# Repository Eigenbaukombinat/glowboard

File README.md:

# Glowboard Plotter

The Glowboard Plotter plots images using 64 UV LEDs attached in a line moved over a 120cmx60cm glow-in-the-dark sheet by a stepper.

More Details see here: https://hackaday.io/project/11868-glowboard-plotter

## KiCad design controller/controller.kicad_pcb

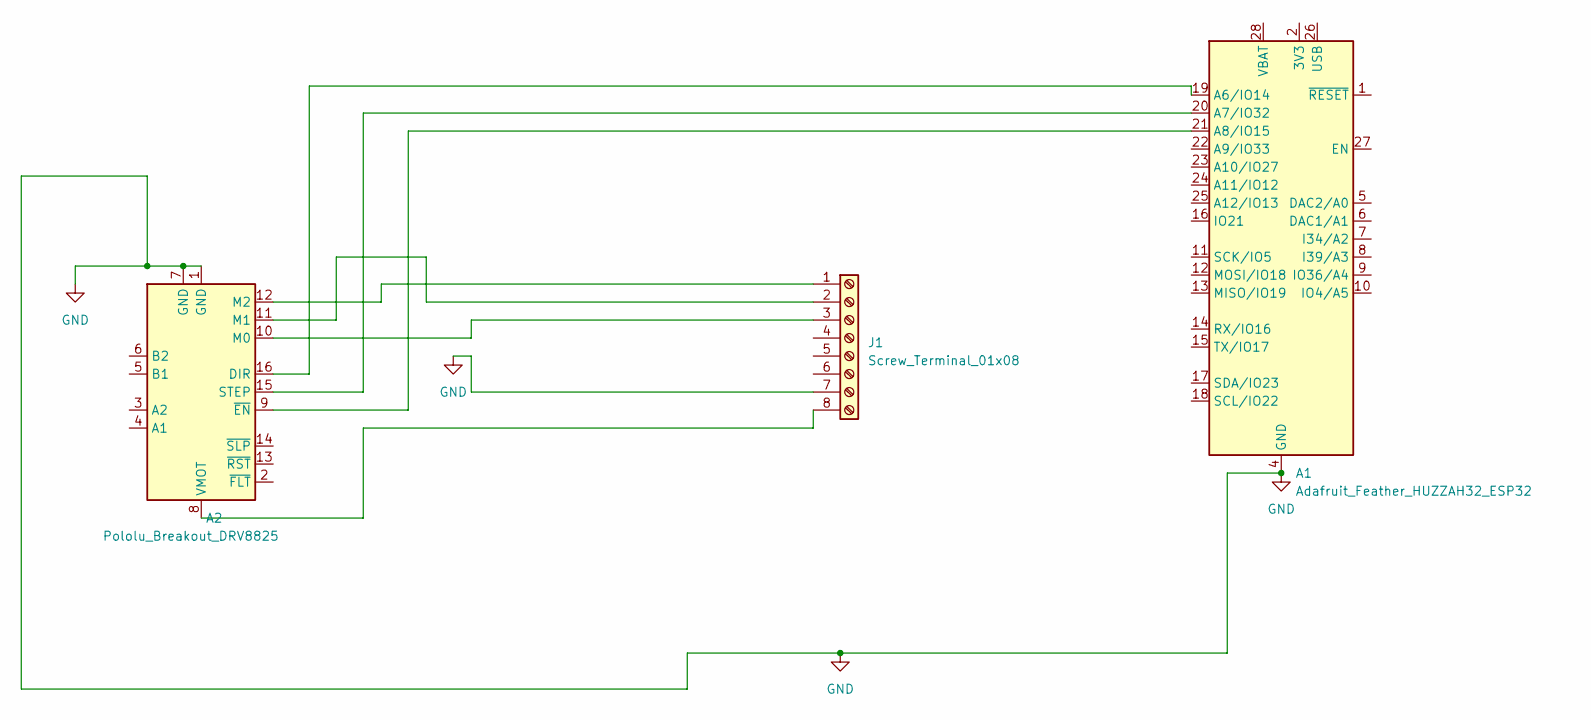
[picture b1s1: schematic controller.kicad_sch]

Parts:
A1: Adafruit_Feather_HUZZAH32_ESP32; Adafruit_Feather
A2: Pololu_Breakout_DRV8825; Pololu_Breakout-16_15.2x20.3mm
J1: Screw_Terminal_01x08; TerminalBlock_4Ucon_1x08_P3.50mm_Horizontal

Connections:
GND: A1.4 (GND), A2.1 (GND), A2.7 (GND), J1.7
unnamed: A1.19 (A6/IO14), A2.16 (DIR)
unnamed: A1.20 (A7/IO32), A2.15 (STEP)
unnamed: A1.21 (A8/IO15), A2.9 (~EN)
unnamed: A2.10 (M0), J1.3
unnamed: A2.11 (M1), J1.2
unnamed: A2.12 (M2), J1.1
unnamed: A2.8 (VMOT), J1.8

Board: 2 copper layers, 3 parts (0 on the bottom side), 8 nets, no tracks yet.

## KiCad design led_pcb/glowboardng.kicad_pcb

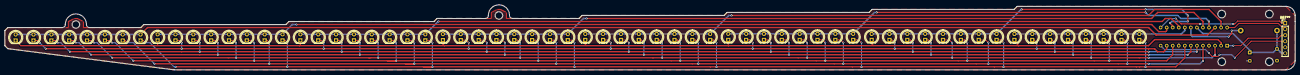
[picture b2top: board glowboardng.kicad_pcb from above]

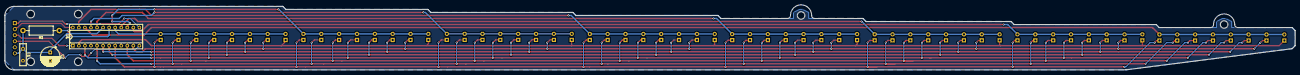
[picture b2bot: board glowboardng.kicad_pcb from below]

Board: 2 copper layers, 542.3 x 27.3 mm, 68 parts (4 on the bottom side), 19 nets.

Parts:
C1: C; C_Disc_D9.0mm_W2.5mm_P5.00mm
C2: C_Polarized; CP_Radial_D8.0mm_P3.50mm
D1, D2, D3, D4, D5, D6, D7, D8, D9, D10, D11, D12, D13, D14, D15, D16, D17, D18, D19, D20, D21, D22, D23, D24, D25, D26, D27, D28, D29, D30, D31, D32, D33, D34, D35, D36, D37, D38, D39, D40, D41, D42, D43, D44, D45, D46, D47, D48, D49, D50, D51, D52, D53, D54, D55, D56, D57, D58, D59, D60, D61, D62, D63, D64: CQY99; LED_D5.0mm_IRGrey
R1: R; R_Axial_DIN0411_L9.9mm_D3.6mm_P15.24mm_Horizontal
U1: MAX7219; DIP-24_W7.62mm_Socket

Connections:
+5V: C1.1, C2.1, R1.2, U1.19 (V+)
GND: C1.2, C2.2, U1.4 (GND), U1.9 (GND)
unnamed: D1.2 (A), D2.2 (A), D3.2 (A), D4.2 (A), D5.2 (A), D6.2 (A), D7.2 (A), D8.2 (A), U1.22 (SEG_DP)
unnamed: D1.1 (K), D9.1 (K), D17.1 (K), D25.1 (K), D33.1 (K), D41.1 (K), D49.1 (K), D57.1 (K), U1.2 (DIG_0)
unnamed: D9.2 (A), D10.2 (A), D11.2 (A), D12.2 (A), D13.2 (A), D14.2 (A), D15.2 (A), D16.2 (A), U1.14 (SEG_A)
unnamed: D2.1 (K), D10.1 (K), D18.1 (K), D26.1 (K), D34.1 (K), D42.1 (K), D50.1 (K), D58.1 (K), U1.11 (DIG_1)
unnamed: D3.1 (K), D11.1 (K), D19.1 (K), D27.1 (K), D35.1 (K), D43.1 (K), D51.1 (K), D59.1 (K), U1.6 (DIG_2)
unnamed: D4.1 (K), D12.1 (K), D20.1 (K), D28.1 (K), D36.1 (K), D44.1 (K), D52.1 (K), D60.1 (K), U1.7 (DIG_3)
unnamed: D5.1 (K), D13.1 (K), D21.1 (K), D29.1 (K), D37.1 (K), D45.1 (K), D53.1 (K), D61.1 (K), U1.3 (DIG_4)
unnamed: D6.1 (K), D14.1 (K), D22.1 (K), D30.1 (K), D38.1 (K), D46.1 (K), D54.1 (K), D62.1 (K), U1.10 (DIG_5)
unnamed: D7.1 (K), D15.1 (K), D23.1 (K), D31.1 (K), D39.1 (K), D47.1 (K), D55.1 (K), D63.1 (K), U1.5 (DIG_6)
unnamed: D8.1 (K), D16.1 (K), D24.1 (K), D32.1 (K), D40.1 (K), D48.1 (K), D56.1 (K), D64.1 (K), U1.8 (DIG_7)
unnamed: D17.2 (A), D18.2 (A), D19.2 (A), D20.2 (A), D21.2 (A), D22.2 (A), D23.2 (A), D24.2 (A), U1.16 (SEG_B)
unnamed: D25.2 (A), D26.2 (A), D27.2 (A), D28.2 (A), D29.2 (A), D30.2 (A), D31.2 (A), D32.2 (A), U1.20 (SEG_C)
unnamed: D33.2 (A), D34.2 (A), D35.2 (A), D36.2 (A), D37.2 (A), D38.2 (A), D39.2 (A), D40.2 (A), U1.23 (SEG_D)
unnamed: D41.2 (A), D42.2 (A), D43.2 (A), D44.2 (A), D45.2 (A), D46.2 (A), D47.2 (A), D48.2 (A), U1.21 (SEG_E)
unnamed: D49.2 (A), D50.2 (A), D51.2 (A), D52.2 (A), D53.2 (A), D54.2 (A), D55.2 (A), D56.2 (A), U1.15 (SEG_F)
unnamed: D57.2 (A), D58.2 (A), D59.2 (A), D60.2 (A), D61.2 (A), D62.2 (A), D63.2 (A), D64.2 (A), U1.17 (SEG_G)
unnamed: R1.1, U1.18 (ISET)

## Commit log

2016-05-14 greet at start
2016-05-14 add info
2016-05-14 Styled up webserver(sesshomariu)
2016-05-14 correct credits
2016-05-14 add some more pics
2016-05-14 remove pngs
2016-05-14 de-obfuscated main html in webserver.py ;)
2016-05-14 high res mode
2016-05-14 new img
2016-05-14 add high res info
2016-05-14 highres t21
2016-05-15 doge highres
2016-05-15 highres ccc
2016-05-15 posthorn
2016-05-15 duino image
2016-05-15 add snowden
2016-05-15 grumpy
2016-05-15 count pool
2016-05-15 inFOU Iz noUW moAR g0ud m8
2016-05-15 Web interface update
2016-05-15 another image
2016-05-15 Added high-res mode to web ui
2016-05-24 add juha.jpg
2016-05-24 note of 256px
2016-05-25 grayscale support
2016-05-25 use correct values for resolution
2016-05-25 fix grayscale mode
2016-05-27 read number of passes out of the filenames of predefined images
2016-05-27 add a few other images to the pool
2016-05-27 werbung
2016-06-09 fix multipass
2023-03-25 update code to python3
2023-04-02 move old stuff
2023-04-02 add pcbs for glowboardNG
2023-04-10 add some drawings
2023-04-10 first working firmware for esp32
2023-06-24 recent changes
